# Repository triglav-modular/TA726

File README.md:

# TA726

Exponetial Converter with a thermal oven for the 208.

This board replaces the uA726 in the 208 / Music Easel with a heated MAT14 / THAT300. 
It has to be mounted from below (to the solder side of CARD 6 & 7), like the pA726.

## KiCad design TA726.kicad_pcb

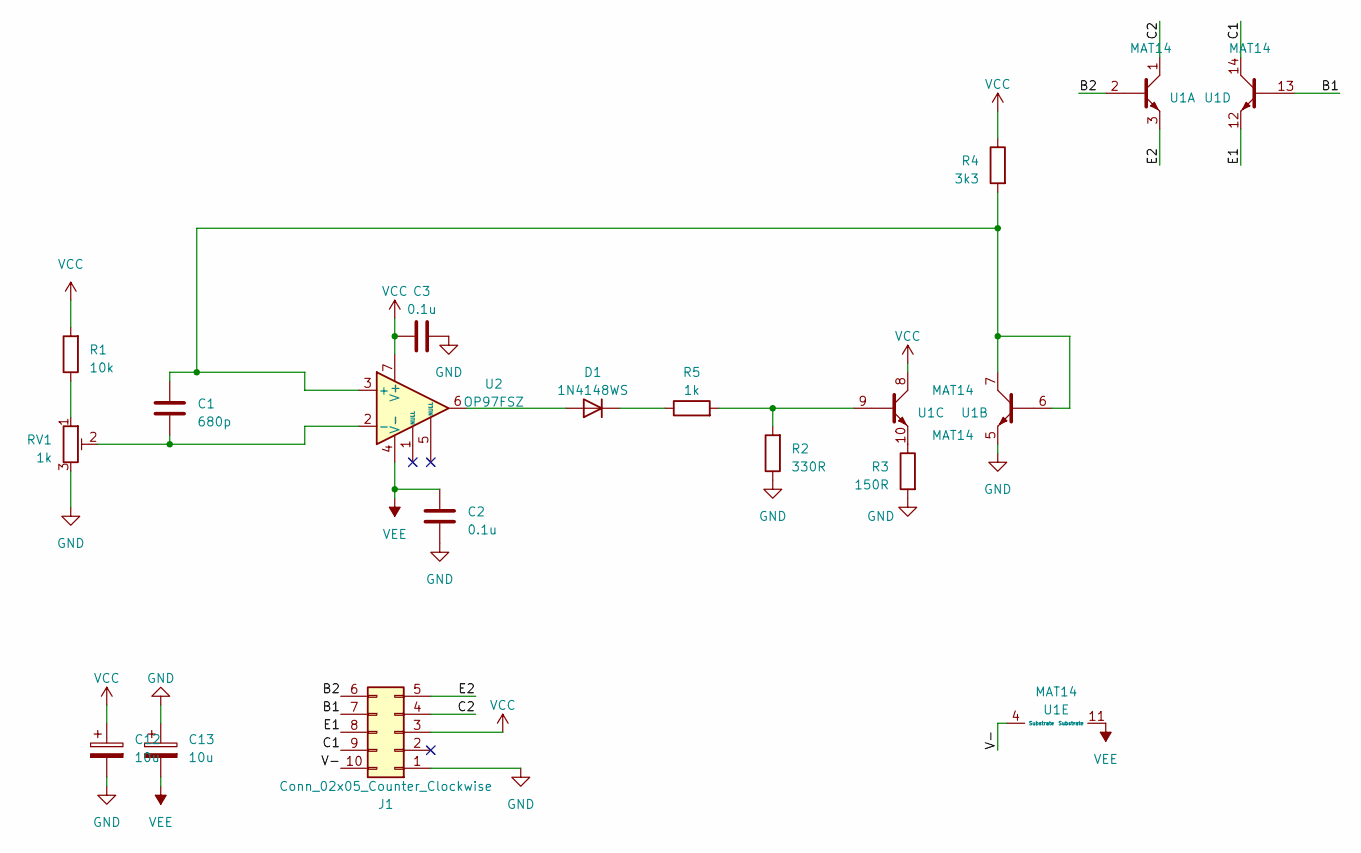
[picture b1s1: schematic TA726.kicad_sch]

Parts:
C1: 680p; C_0603_1608Metric
C2, C3: 0.1u; C_0603_1608Metric
C12, C13: 10u; CP_Elec_4x5.8
D1: 1N4148WS; D_SOD-323
J1: Conn_02x05_Counter_Clockwise; DIP-10_W8.89mm_SMDSocket_LongPads
R1: 10k; R_0603_1608Metric
R2: 330R; R_0603_1608Metric
R3: 150R; R_0603_1608Metric
R4: 3k3; R_0603_1608Metric
R5: 1k; R_0603_1608Metric
RV1: 1k; Potentiometer_Bourns_3266P_Horizontal
U1: MAT14; SO-14_3.9x8.65mm_P1.27mm
U2: OP97FSZ; SO-8_3.9x4.9mm_P1.27mm

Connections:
/B1: J1.7, U1.13 (B)
/B2: J1.6, U1.2 (B)
/C1: J1.9, U1.14 (C)
/C2: J1.4, U1.1 (C)
/E1: J1.8, U1.12 (E)
/E2: J1.5, U1.3 (E)
/V-: J1.10, U1.4 (Substrate)
GND: C2.2, C3.2, C12.2, C13.1, J1.1, R2.1, R3.2, RV1.3, U1.5 (E)
unnamed: D1.2 (A), U2.6
unnamed: D1.1 (K), R5.1
unnamed: R1.1, RV1.1
unnamed: C1.1, R4.2, U1.6 (B), U1.7 (C), U2.3 (+)
unnamed: R2.2, R5.2, U1.9 (B)
unnamed: R3.1, U1.10 (E)
unnamed: C1.2, RV1.2, U2.2 (-)
VCC: C3.1, C12.1, J1.3, R1.2, R4.1, U1.8 (C), U2.7 (V+)
VEE: C2.1, C13.2, U1.11 (Substrate), U2.4 (V-)

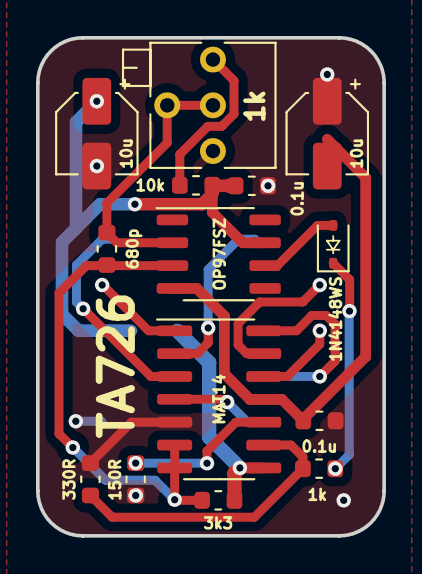
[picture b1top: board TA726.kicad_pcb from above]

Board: 2 copper layers, 19.2 x 27.7 mm, 15 parts (1 on the bottom side), 17 nets.

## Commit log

2023-02-21 rotated trimmer
2023-02-21 3d models
